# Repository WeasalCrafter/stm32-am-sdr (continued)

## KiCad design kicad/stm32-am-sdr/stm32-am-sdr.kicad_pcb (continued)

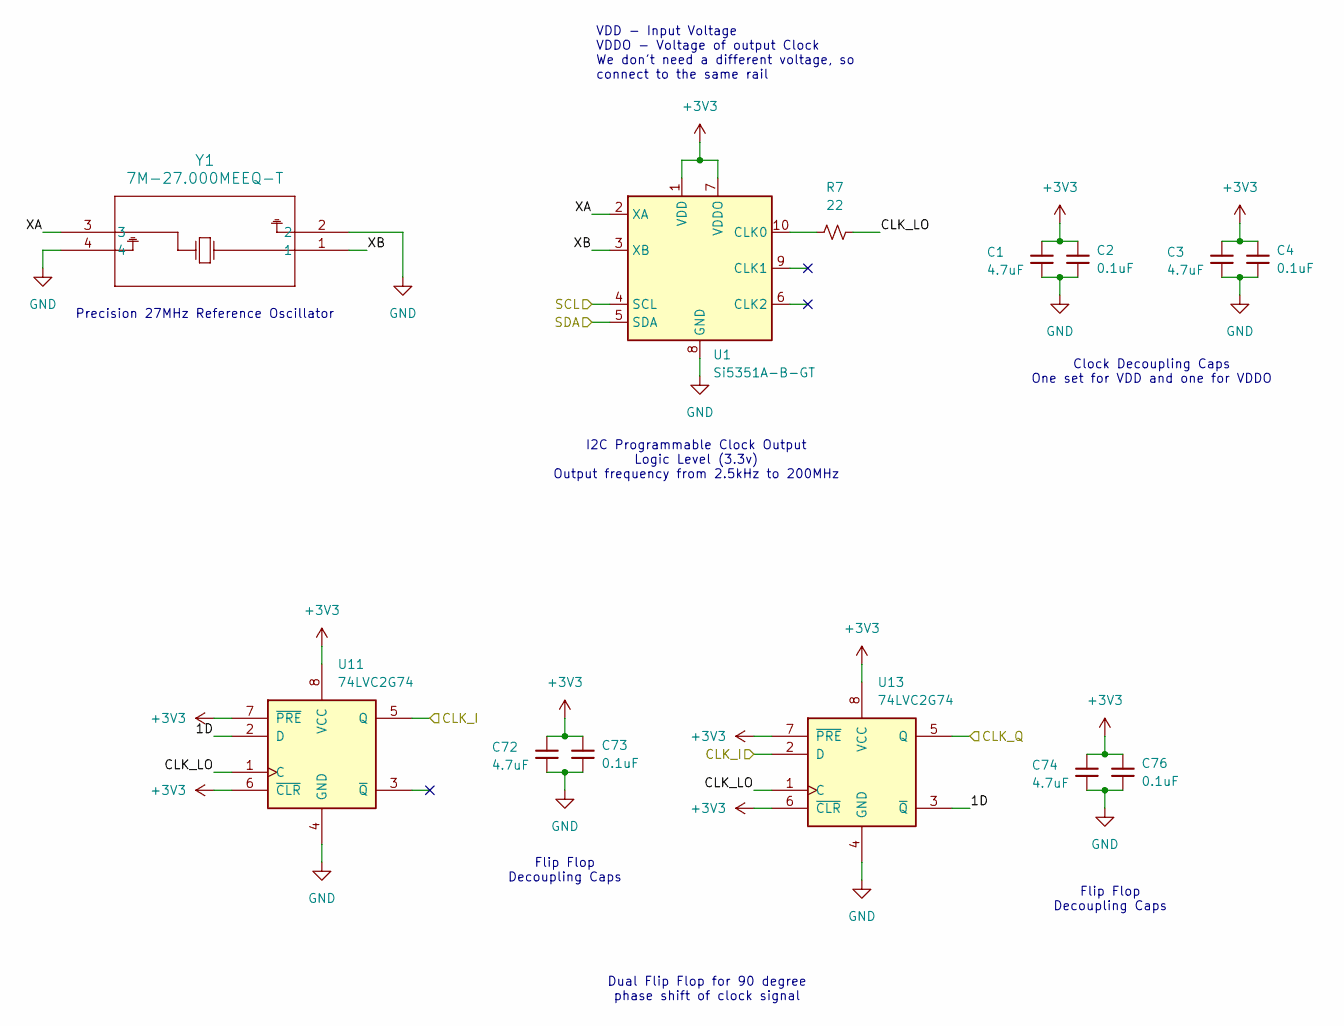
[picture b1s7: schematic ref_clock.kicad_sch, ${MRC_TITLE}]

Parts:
C1, C3, C72, C74: 4.7uF; C_0603_1608Metric; digikey_id 311-1785-1-ND
C2, C4, C73, C76: 0.1uF; C_0603_1608Metric; digikey_id 311-1779-1-ND
R7: 22; R_0603_1608Metric; digikey_id RMCF0603FT22R0CT-ND
U1: Si5351A-B-GT; MSOP-10_3x3mm_P0.5mm; digikey_id 336-5445-ND
U11, U13: 74LVC2G74; VSSOP-8_2.3x2mm_P0.5mm; digikey_id 296-21820-1-ND
Y1: 7M-27.000MEEQ-T; Crystal_SMD_3225-4Pin_3.2x2.5mm; digikey_id 887-1328-2-ND

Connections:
+3V3: C1.1, C2.1, C3.1, C4.1, C72.1, C73.1, C74.1, C76.1, U1.1 (VDD), U1.7 (VDDO), U11.6 (~CLR), U11.7 (~PRE), U11.8 (VCC), U13.6 (~CLR), U13.7 (~PRE), U13.8 (VCC); also elsewhere on the board
/CLK_I: U11.5 (Q), U13.2 (D); also elsewhere on the board
/CLK_Q: U13.5 (Q); also elsewhere on the board
/Reference Clock/1D: U11.2 (D), U13.3 (~Q)
/Reference Clock/CLK_LO: R7.2, U11.1 (C), U13.1 (C)
/Reference Clock/XA: U1.2 (XA), Y1.3
/Reference Clock/XB: U1.3 (XB), Y1.1
/SCL: U1.4 (SCL); also elsewhere on the board
/SDA: U1.5 (SDA); also elsewhere on the board
GND: C1.2, C2.2, C3.2, C4.2, C72.2, C73.2, C74.2, C76.2, U1.8 (GND), U11.4 (GND), U13.4 (GND), Y1.2, Y1.4; also elsewhere on the board
unnamed: R7.1, U1.10 (CLK0)

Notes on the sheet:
VDD - Input Voltage VDDO - Voltage of output Clock We don't need a different voltage, so connect to the same rail
Dual Flip Flop for 90 degree phase shift of clock signal
I2C Programmable Clock Output Logic Level (3.3v) Output frequency from 2.5kHz to 200MHz
Precision 27MHz Reference Oscillator
Clock Decoupling Caps One set for VDD and one for VDDO
Flip Flop Decoupling Caps

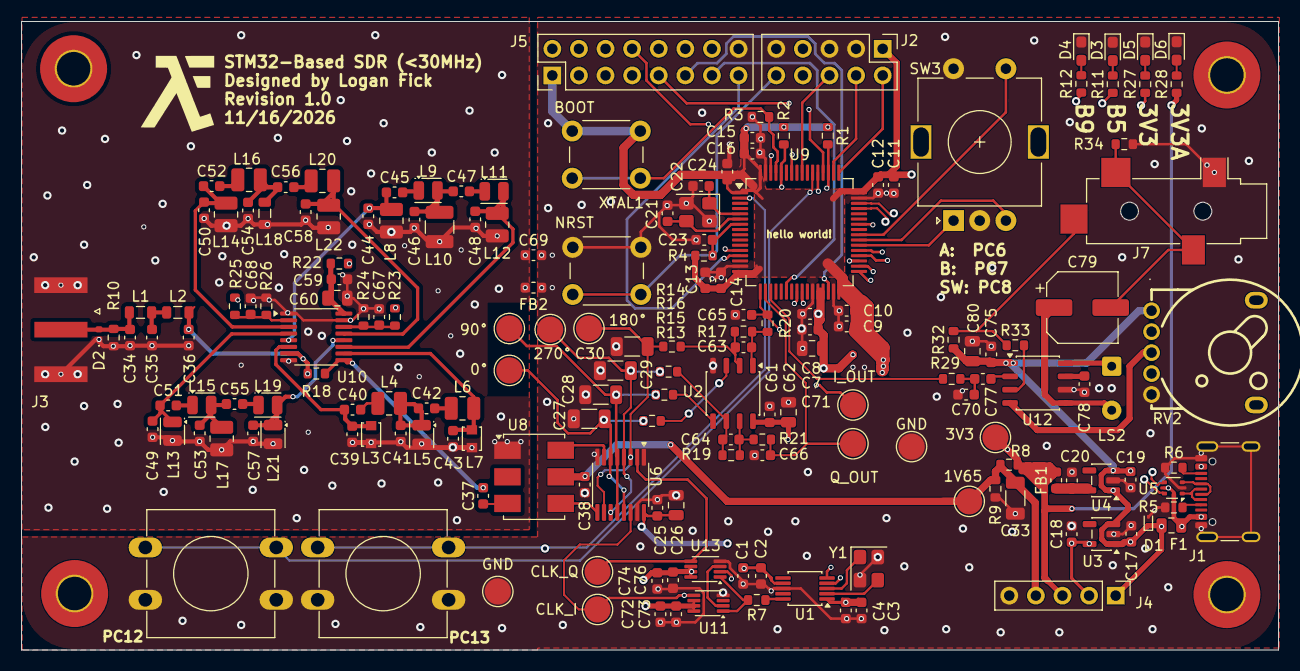
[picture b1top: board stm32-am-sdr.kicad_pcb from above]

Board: 4 copper layers, 120.0 x 60.0 mm, 182 parts (0 on the bottom side), 107 nets.

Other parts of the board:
0°, 1V65, 3V3, 90°, 180°, 270°: TestPoint; TestPoint_Pad_D2.5mm
BOOT: BOOT; SW_PUSH_6mm_H4.3mm
CLK_I: TestPoint; TestPoint_Pad_D2.5mm
CLK_Q: TestPoint; TestPoint_Pad_D2.5mm
GND: TestPoint; TestPoint_Pad_D2.5mm
GND#2: TestPoint; TestPoint_Pad_D2.5mm
I_OUT: TestPoint; TestPoint_Pad_D2.5mm
NRST: RESET; SW_PUSH_6mm_H4.3mm
PC12, PC13: SW_Push; SW_PUSH-12mm
Q_OUT: TestPoint; TestPoint_Pad_D2.5mm

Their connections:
+1V65: 1V65.1 (1_1); also elsewhere on the board
+3V3: BOOT.1; also elsewhere on the board
+3V3A: 3V3.1 (1_1); also elsewhere on the board
/CLK_I: CLK_I.1 (1_1); also elsewhere on the board
/CLK_Q: CLK_Q.1 (1_1); also elsewhere on the board
/I_OUT: I_OUT.1 (1_1); also elsewhere on the board
/Q_OUT: Q_OUT.1 (1_1); also elsewhere on the board
/RF Input and Tayloe Detector/0A: 0°.1 (1_1); also elsewhere on the board
/RF Input and Tayloe Detector/0B: 180°.1 (1_1); also elsewhere on the board
/RF Input and Tayloe Detector/270A: 270°.1 (1_1); also elsewhere on the board
/RF Input and Tayloe Detector/270B: 90°.1 (1_1); also elsewhere on the board
/STM32 Microcontroller/BOOT0: BOOT.2; also elsewhere on the board
/STM32 Microcontroller/NRST: NRST.2; also elsewhere on the board
/STM32 Microcontroller/PC12: PC12.1; also elsewhere on the board
/STM32 Microcontroller/PC13: PC13.1; also elsewhere on the board
GND: GND.1 (1_1), GND#2.1 (1_1), NRST.1, PC12.2, PC13.2; also elsewhere on the board
